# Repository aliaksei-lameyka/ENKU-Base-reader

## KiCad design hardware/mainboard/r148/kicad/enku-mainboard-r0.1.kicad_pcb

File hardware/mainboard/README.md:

# ENKU Base mainboard

Current working PCB **R144 / NO FAB**, branch `engineering/r144-power-margin`. [Project](r144/kicad/enku-mainboard-r0.1.kicad_pro), [review packet](r144/pcbway/), [source/checkpoint](r144/README.md), [current status](../../docs/CURRENT_STATUS.md).

TPS3890 reset + nominal3.220352V PWM supply. Full native/independent local and [server verification](https://github.com/aliaksei-lameyka/ENKU-Base-reader/actions/runs/38693384483) passed. Initial/solder static reserves pass; lifetime/dynamic, FPC/pack/process/firmware and physical tests remain open. See [risks](../../docs/STARTUP_RISKS_R144.md), [FPC](../../docs/FPC_CONNECTOR_REVIEW_R144.md), [pilot FCT](../../docs/FCT_PLAN_R144.md). Physical tests NOT RUN. No case-thickness increase or Base dock/frontlight/Hall/Qi.

`kicad/` is immutable R138. R141/R142/R143 are historical controls. No historical guard/golden was changed. Hardware CERN-OHL-W-2.0, automation MIT.

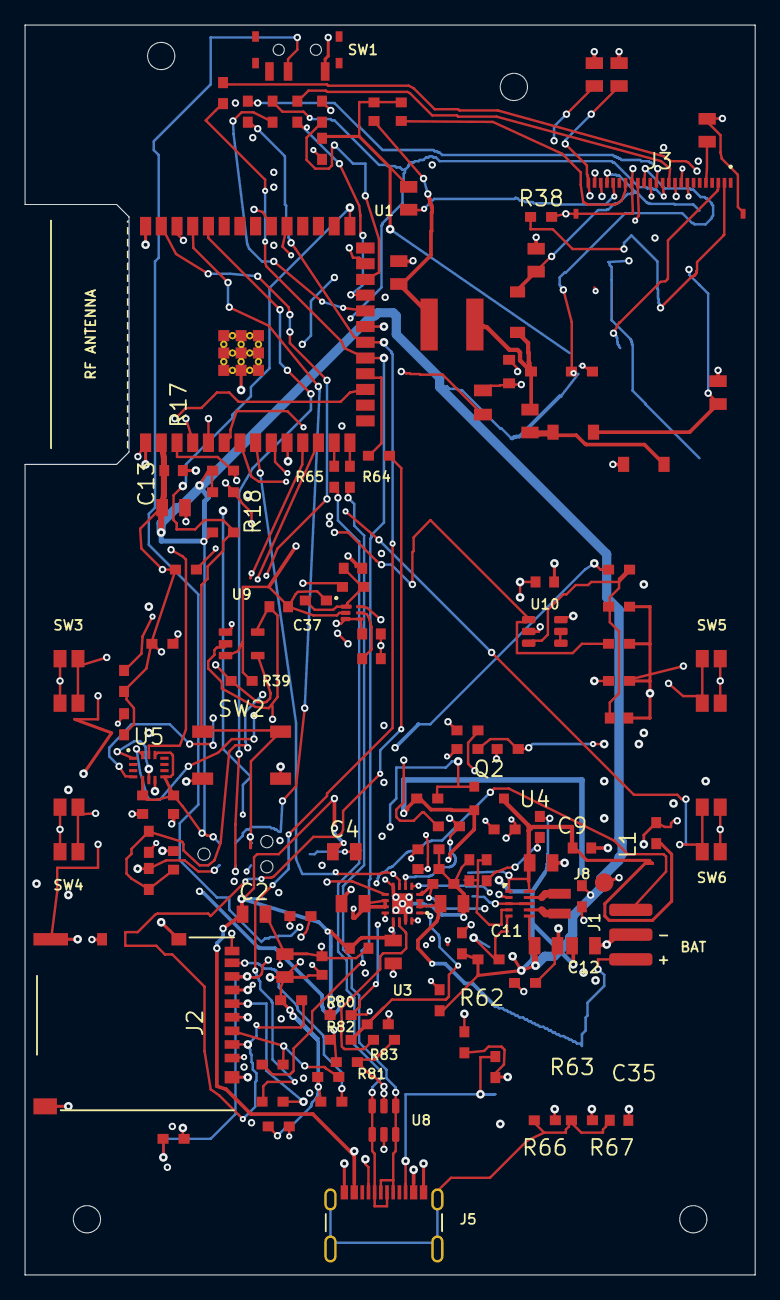
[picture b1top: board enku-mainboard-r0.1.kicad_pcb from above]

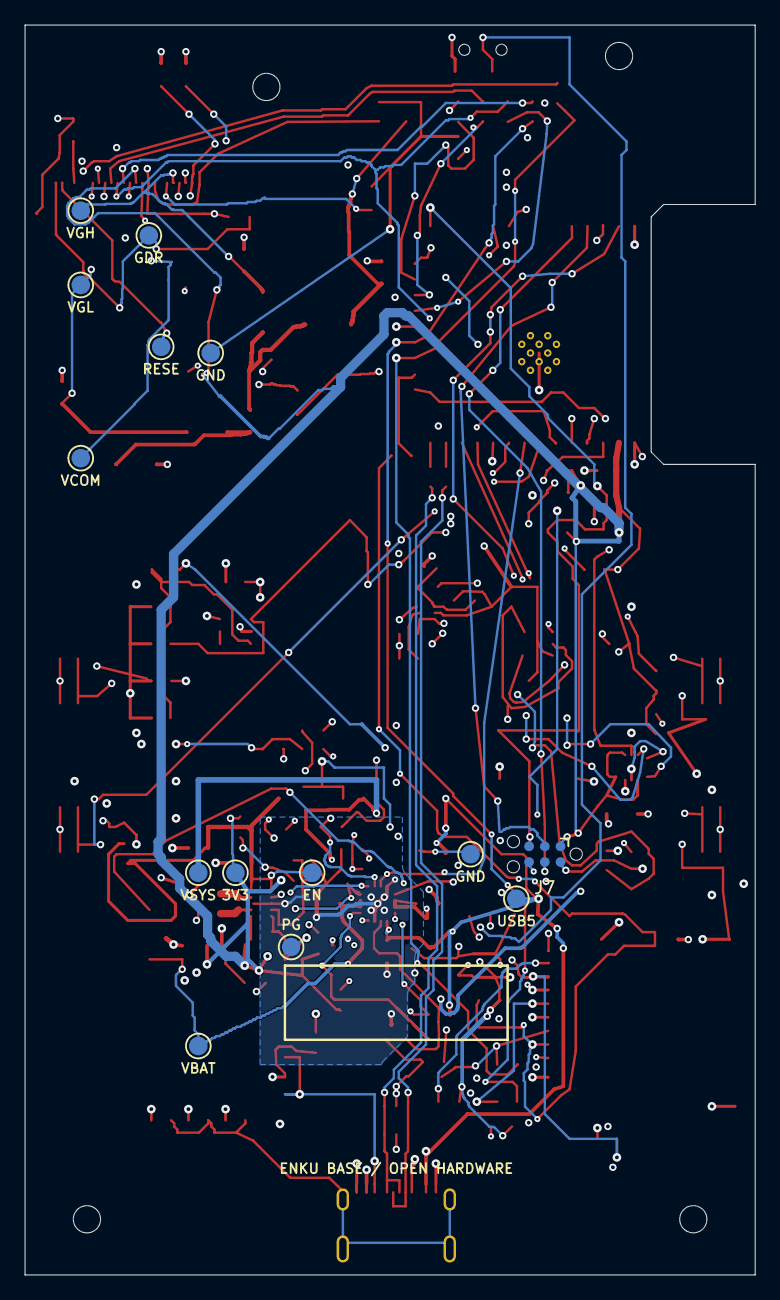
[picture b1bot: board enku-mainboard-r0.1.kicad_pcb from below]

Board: 4 copper layers, 59.0 x 101.0 mm, 141 parts (14 on the bottom side), 84 nets.

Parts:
C2: 1uF 10V; C_CC0805_YAGEO_REFLOW_TRANSFER
C4: 1uF 25V; C_CC0805_YAGEO_REFLOW_TRANSFER
C5, C24, C25, C26, C27, C28, C29, C31: 4.7uF 25V; C_CC0805_YAGEO_REFLOW_TRANSFER
C6: 100nF 25V; C_CC0603_YAGEO_REFLOW_TRANSFER
C7, C8, C9, C11, C12: 22uF 10V; C_CC0805_YAGEO_REFLOW_TRANSFER
C10, C14, C15, C17, C18, C19, C21, C40: 100nF; C_CC0603_YAGEO_REFLOW_TRANSFER
C13, C16: 10uF 10V; C_CC0805_YAGEO_REFLOW_TRANSFER
C22, C23: 1uF 25V; C_CC0603_YAGEO_REFLOW_TRANSFER
C30: 1uF 25V X7R; C_CC0805_YAGEO_REFLOW_TRANSFER
C35: 4.7nF; C_CC0603_YAGEO_REFLOW_TRANSFER
C37, C38: 100nF 10V; C_CC0603_YAGEO_REFLOW_TRANSFER
C39: 1nF C0G 10V; C_CC0603_YAGEO_REFLOW_TRANSFER
C41: 1nF 50V; C_CC0603_YAGEO_REFLOW_TRANSFER
D1, D2, D3: MBR0530T1G; MBR0530T1G_ONSEMI_CASE425H
H1, H2, H3, H4: MOUNT_HOLE_D2_2_BOARD_ONLY
J1: BATTERY_WIRES; BATTERY_WIRE_PADS_2x1x3p5_P2_NO_PASTE
J2: Hirose DM3AT-SF-PEJM5; MICROSD_DM3AT_ENKU
J3: FH34SRJ-24S-0.5SH(50); FH34SRJ-24S-0.5SH
J5: GCT USB4215-03-A; USB4215_03_A_GCT_REVA
J7: Tag-Connect TC2030-IDC-NL; TC2030_NL_CONTACTS_PIN1
J8: External cell NTC / hand solder; NTC_WIRE_TERMINALS_TS_BAR_GND_NO_PASTE
L1: 0.47uH DFE201612E-R47M=P2; Murata_DFE201612E
L2: 47uH TYS5040470M-10; TYS5040_LAIRD_G42_T14_H23
Q1: IRLML6346TRPBF; IRLML6346_INFINEON_MICRO3
Q2: AO3401A; AO3401A_AOS_SOT23
R8: 3.48k 1%; R_RC0603_YAGEO_REFLOW
R9: 2k 1%; R_RC0603_YAGEO_REFLOW
R10, R13, R16, R35, R36, R72: 100k; R_RC0603_YAGEO_REFLOW
R11, R12, R17, R18, R23, R90, R91, R92, R93, R94: 10k; R_RC0603_YAGEO_REFLOW
R14: 27.4k 0.1% 10ppm; R_RT0603_YAGEO_REFLOW
R15: 5.11k 0.1% 10ppm; R_RT0603_YAGEO_REFLOW
R19, R28, R29, R97: 0R; R_RC0603_YAGEO_REFLOW
R20, R21, R22, R64, R65: 0R (22R tune); R_RC0603_YAGEO_REFLOW
R24, R25: 4.7k; R_RC0603_YAGEO_REFLOW
R26: 2M 1%; R_RC0603_YAGEO_REFLOW
R27: 680k 1%; R_RC0603_YAGEO_REFLOW
R30, R31, R32, R33, R34: 22R; R_RC0603_YAGEO_REFLOW
R37: 2.2R 1% 0805; R_CRCW0805_HP_VISHAY_REFLOW
R38: 1M 1%; R_RC0603_YAGEO_REFLOW
R39, R66: 1M; R_RC0603_YAGEO_REFLOW
R40, R82: 100k 1%; R_RC0603_YAGEO_REFLOW
R62, R63: 5.1k 1%; R_RC0603_YAGEO_REFLOW
R67: 0R DNP; R_RC0603_YAGEO_REFLOW_DNP_NO_PASTE
R70: 26.7k 0.1% 25ppm; R_RT0603_YAGEO_REFLOW
R71: 10k 0.1% 25ppm; R_RT0603_YAGEO_REFLOW
R73: 3.3k 1%; R_RC0603_YAGEO_REFLOW
R80: 40.2k 1%; R_RC0603_YAGEO_REFLOW
R81: 33.2k 1%; R_RC0603_YAGEO_REFLOW
R83: 69.8k 1%; R_RC0603_YAGEO_REFLOW
R84, R85: 2.2k 1%; R_RC0603_YAGEO_REFLOW
R86, R87, R88: 1k 1%; R_RC0603_YAGEO_REFLOW
R89: 3.3M 1%; R_RC0603_YAGEO_REFLOW
R95: 16.5k 0.1% 10ppm; R_RT0603_YAGEO_REFLOW
R96: 10k 0.1% 10ppm; R_RT0603_YAGEO_REFLOW
R98: 402R 0.1% 10ppm; R_RT0603_YAGEO_REFLOW
R99: 0R; R_RC0603_YAGEO_REFLOW_DNP_NO_PASTE
SW1: MK-12C03-G015; GSWITCH_MK12C03_G015_DRAWING_REVIEW
SW2: BOOT / RECOVERY; TL3342F160QG_ESWITCH_P010632J
SW3, SW4, SW5, SW6: TL1016AAF160QG; TL1016AAF160QG_ESWITCH_P520001
TP1, TP14: GND; SERVICE_PAD_D1_5_NO_PASTE
TP2: VBUS_USB; SERVICE_PAD_D1_5_NO_PASTE
TP4: VBAT; SERVICE_PAD_D1_5_NO_PASTE
TP5: VSYS; SERVICE_PAD_D1_5_NO_PASTE
TP6: 3V3_SYS; SERVICE_PAD_D1_5_NO_PASTE
TP7: SYS_EN; SERVICE_PAD_D1_5_NO_PASTE
TP8: REG_PG; SERVICE_PAD_D1_5_NO_PASTE
TP9: EPD_GDR; SERVICE_PAD_D1_5_NO_PASTE
TP10: EPD_RESE; SERVICE_PAD_D1_5_NO_PASTE
TP11: EPD_VGH; SERVICE_PAD_D1_5_NO_PASTE
TP12: EPD_VGL; SERVICE_PAD_D1_5_NO_PASTE
TP13: EPD_VCOM; SERVICE_PAD_D1_5_NO_PASTE
U1: ESP32-S3-WROOM-1-N16R8; ESP32_S3_WROOM_1_N16R8_EP_GRID_03_TENT_REQUEST
U3: BQ24072TRGTR; BQ24072T_RGT0016C_TI
U4: TPS63802DLAR; TPS63802_DLA0010A_SPLIT_PASTE
U5: BMI270; BMI270_Bosch_LGA14
U8: USBLC6-2SC6; USBLC6_2SC6_ST_SOT23_6L
U9: TMUX1101DBVR; TMUX1101_TI_DBV0005A
U10: TLV3012BIDBVR; TLV3012B_DBV0006A
U11: TPS389001DSER; TPS3890_TI_DSE0006A_SMD_LEFT

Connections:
3V3_SYS: C11.1, C12.1, C13.1, C14.1, C15.1, C16.1, C17.1, C18.1, C19.1, C38.1, J2.4, J3.15, J7.1, R11.1, R12.1, R16.1, R17.1, R18.1, R23.1, R24.1, R25.1, R28.1, R35.1, R36.1, R39.1, R90.1, R91.1, R92.1, R93.1, R94.1, R95.1, R97.1, R98.1, TP6.1, U1.2, U4.6, U5.5, U5.8, U5.12, U9.4, U10.6, U11.3, U11.4
BAT_ADC: C21.1, R26.2, R27.1, U1.39
BAT_ADC_SW: R26.1, U9.1
BAT_TS: J8.1, R80.2, R81.1, R82.1
BOOT: J7.5, R18.2, SW2.1, U1.27
BTN_L1: SW3.1, SW3.2, U1.4
BTN_L2: SW4.1, SW4.2, U1.5
BTN_R1: SW5.1, SW5.2, U1.6
BTN_R2: SW6.1, SW6.2, U1.7
CHG_CE_CMD: R88.1, U1.31
CHG_CE_N: R10.1, R88.2, U3.4
CHG_EN1: R84.1, R86.2, U3.6
CHG_EN1_CMD: R86.1, U1.9
CHG_EN2: R85.1, R87.2, U3.5
CHG_EN2_CMD: R87.1, U1.38
CHG_ILIM_VSET: R8.1, U3.12
CHG_ISET: R9.1, U3.16
CHG_STAT1: R11.2, U1.8, U3.7
CHG_STAT2: R12.2, U3.9
CHG_TMR: R83.1, U3.14
CHG_TS: R82.2, R89.1, U3.1
EPD_BS1: J3.8, R29.1
EPD_BUSY: J3.9, U1.25
EPD_CP_NEG: C25.2, D2.2, D3.1
EPD_CS: R32.1, U1.22
EPD_CS_PANEL: J3.12, R32.2, R35.2
EPD_DC: R31.1, U1.23
EPD_DC_PANEL: J3.11, R31.2
EPD_GDR: J3.2, Q1.1, R38.1, TP9.1
EPD_MOSI_PANEL: J3.14, R34.2
EPD_RESE: J3.3, Q1.2, R37.1, TP10.1
EPD_RST: R30.1, U1.24
EPD_RST_PANEL: J3.10, R30.2, R36.2
EPD_SCLK_PANEL: J3.13, R33.2
EPD_SW: C25.1, D1.2, L2.2, Q1.3
EPD_VCI: C22.1, C31.1, J3.16, L2.1, R28.2
EPD_VCOM: C30.1, J3.24, TP13.1
EPD_VDD: C23.1, J3.18
EPD_VGH: C24.1, D1.1, J3.21, TP11.1
EPD_VGL: C26.1, D3.2, J3.23, TP12.1
EPD_VSH1: C27.1, J3.20
EPD_VSH2: C28.1, J3.5
EPD_VSL: C29.1, J3.22
ESP_EN: J7.6, R17.2, U1.3, U11.6
GND: C2.2, C4.2, C5.2, C6.2, C7.2, C8.2, C9.2, C10.2, C11.2, C12.2, C13.2, C14.2, C15.2, C16.2, C17.2, C18.2, C19.2, C21.2, C22.2, C23.2, C24.2, C26.2, C27.2, C28.2, C29.2, C30.2, C31.2, C35.2, C37.2, C38.2, C39.2, C40.2, C41.2, D2.1, J1.2, J2.6, J2.10 (CD_B), J3.17, J3.S1, J3.S2, J5.A1, J5.A12, J5.B1, J5.B12, J7.2, J8.2, R8.2, R9.2, R10.2, R13.2, R15.2, R27.2, R29.2, R37.2, R38.2, R39.2, R62.2, R63.2, R66.2, R67.2, R71.2, R72.2, R73.2, R81.2, R83.2, R84.2, R85.2, R89.2, R96.2, R99.2, SW1.1, SW2.2, SW3.3, SW3.4, SW4.3, SW4.4, SW5.3, SW5.4, SW6.3, SW6.4, TP1.1, TP14.1, U1.1, U1.40, U1.41, U3.8, U3.15, U3.17, U4.3, U4.8, U5.1, U5.6, U5.7, U8.2, U9.3, U10.2, U11.2
I2C_SCL: R25.2, U1.17, U5.13
I2C_SDA: R24.2, U1.12, U5.14
IMU_INT1: U1.11, U5.4
PWR_GATE: Q2.1, R40.2, SW1.2
REG_FB: R14.2, R15.1, U4.4
REG_FB_TOP: R14.1, R98.2
REG_L1: L1.1, U4.9
REG_L2: L1.2, U4.7
REG_MODE: R97.2, R99.1, U4.2
REG_PG: R16.2, TP8.1, U4.5
RESET_CT: C40.1, U11.5
RESET_SENSE: C41.1, R95.2, R96.1, U11.1
SD_CD: J2.9 (CD_A), R90.2, U1.32
SD_CS: R19.1, U1.18
SD_CS_CARD: J2.2, R19.2, R23.2
SD_DAT1_BIAS: J2.8, R93.2
SD_DAT2_BIAS: J2.1, R94.2
SD_MISO_CARD: J2.7, R22.1, R92.2
SD_MOSI_CARD: J2.3, R20.2, R91.2
SD_SCLK_CARD: J2.5, R21.2
SPI_MISO: R22.2, U1.21
SPI_MOSI: R20.1, R34.1, U1.19
SPI_SCLK: R21.1, R33.1, U1.20
SYS_EN: C9.1, C10.1, Q2.3, R13.1, TP7.1, U4.1, U4.10
UART_RX: J7.4, U1.36
UART_TX: J7.3, U1.37
USB_CC1: J5.A5, R62.1
USB_CC2: J5.B5, R63.1
USB_DM: R65.2, U1.13
USB_DM_CONN: J5.A7, J5.B7, R65.1, U8.3, U8.4
USB_DP: R64.2, U1.14
USB_DP_CONN: J5.A6, J5.B6, R64.1, U8.1, U8.6
USB_SHIELD: C35.1, J5.S, R66.1, R67.1
USB_VBUS_DIV: C39.1, R70.2, R71.1, U10.3
USB_VBUS_REF: U10.4, U10.5
USB_VBUS_VALID: R72.1, U1.10, U10.1
VBAT: C8.1, C37.1, J1.1, TP4.1, U3.2, U3.3, U9.2, U9.5
VBUS_USB: C2.1, C4.1, C5.1, C6.1, J5.A4, J5.A9, J5.B4, J5.B9, R70.1, R73.1, R80.1, TP2.1, U3.13, U8.5
VSYS: C7.1, Q2.2, R40.1, TP5.1, U3.10, U3.11

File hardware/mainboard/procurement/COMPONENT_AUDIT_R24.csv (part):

"ref","value","footprint","side","x_mm","y_mm","rotation_deg","manufacturer","mpn_candidate","preferred_source","manufacturer_drawing","status","footprint_checked","pinout_checked","orientation_checked","cad_checked","pcbway_sourcing_confirmed","review_note"
"C1","100nF","Capacitor_SMD:C_0603_1608Metric","F","64","79","0","","","","","UNSELECTED","NO","NO","NO","NO","NO","Exact orderable passive MPN/voltage/tolerance not selected"
"C2","10uF 10V","Capacitor_SMD:C_0805_2012Metric","F","36.5","92.5","0","","","","","UNSELECTED","NO","NO","NO","NO","NO","Exact orderable passive MPN/voltage/tolerance not selected"
"C3","10uF 10V","Capacitor_SMD:C_0805_2012Metric","F","40","93","0","","","","","UNSELECTED","NO","NO","NO","NO","NO","Exact orderable passive MPN/voltage/tolerance not selected"
"C4","10uF 10V","Capacitor_SMD:C_0805_2012Metric","F","43.8","86.8","0","","","","","UNSELECTED","NO","NO","NO","NO","NO","Exact orderable passive MPN/voltage/tolerance not selected"
"C5","4.7uF 25V","Capacitor_SMD:C_0805_2012Metric","F","45.5","88.5","0","","","","","UNSELECTED","NO","NO","NO","NO","NO","Exact orderable passive MPN/voltage/tolerance not selected"
"C6","100nF 25V","Capacitor_SMD:C_0603_1608Metric","F","47.35","87.75","270","","","","","UNSELECTED","NO","NO","NO","NO","NO","Exact orderable passive MPN/voltage/tolerance not selected"
"C7","10uF 25V","Capacitor_SMD:C_0805_2012Metric","F","51.0","93.5","90","","","","","UNSELECTED","NO","NO","NO","NO","NO","Exact orderable passive MPN/voltage/tolerance not selected"
"C8","4.7uF 10V","Capacitor_SMD:C_0805_2012Metric","F","48.5","93.6","180","","","","","UNSELECTED","NO","NO","NO","NO","NO","Exact orderable passive MPN/voltage/tolerance not selected"
"C9","10uF 10V","Capacitor_SMD:C_0805_2012Metric","F","59.7","87.7","0","","","","","UNSELECTED","NO","NO","NO","NO","NO","Exact orderable passive MPN/voltage/tolerance not selected"
"C10","100nF","Capacitor_SMD:C_0603_1608Metric","F","63","86.5","0","","","","","UNSELECTED","NO","NO","NO","NO","NO","Exact orderable passive MPN/voltage/tolerance not selected"
"C11","22uF 10V","Capacitor_SMD:C_0805_2012Metric","F","60.1","94.4","0","","","","","UNSELECTED","NO","NO","NO","NO","NO","Exact orderable passive MPN/voltage/tolerance not selected"
"C12","22uF 10V","Capacitor_SMD:C_0805_2012Metric","F","63.3","94.4","0","","","","","UNSELECTED","NO","NO","NO","NO","NO","Exact orderable passive MPN/voltage/tolerance not selected"
"C13","10uF 10V","Capacitor_SMD:C_0805_2012Metric","F","23.8","56.2","0","","","","","UNSELECTED","NO","NO","NO","NO","NO","Exact orderable passive MPN/voltage/tolerance not selected"
"C14","100nF","Capacitor_SMD:C_0603_1608Metric","F","27","56.2","0","","","","","UNSELECTED","NO","NO","NO","NO","NO","Exact orderable passive MPN/voltage/tolerance not selected"
"C15","1uF","Capacitor_SMD:C_0603_1608Metric","F","26.5","58.5","0","","","","","UNSELECTED","NO","NO","NO","NO","NO","Exact orderable passive MPN/voltage/tolerance not selected"
"C16","10uF 10V","Capacitor_SMD:C_0805_2012Metric","F","39","96","90","","","","","UNSELECTED","NO","NO","NO","NO","NO","Exact orderable passive MPN/voltage/tolerance not selected"
"C17","100nF","Capacitor_SMD:C_0603_1608Metric","F","42","96","90","","","","","UNSELECTED","NO","NO","NO","NO","NO","Exact orderable passive MPN/voltage/tolerance not selected"
"C18","100nF","Capacitor_SMD:C_0603_1608Metric","F","22","77","90","","","","","UNSELECTED","NO","NO","NO","NO","NO","Exact orderable passive MPN/voltage/tolerance not selected"
"C19","100nF","Capacitor_SMD:C_0603_1608Metric","F","24","80","90","","","","","UNSELECTED","NO","NO","NO","NO","NO","Exact orderable passive MPN/voltage/tolerance not selected"
"C20","100nF","Capacitor_SMD:C_0603_1608Metric","F","72","52","90","","","","","UNSELECTED","NO","NO","NO","NO","NO","Exact orderable passive MPN/voltage/tolerance not selected"
"C21","100nF","Capacitor_SMD:C_0603_1608Metric","F","30","87.5","90","","","","","UNSELECTED","NO","NO","NO","NO","NO","Exact orderable passive MPN/voltage/tolerance not selected"
"C22","1uF 25V","Capacitor_SMD:C_0603_1608Metric","F","46.2","27","90","","","","","UNSELECTED","NO","NO","NO","NO","NO","Exact orderable passive MPN/voltage/tolerance not selected"
"C23","1uF 25V","Capacitor_SMD:C_0603_1608Metric","F","48.4","27","90","","","","","UNSELECTED","NO","NO","NO","NO","NO","Exact orderable passive MPN/voltage/tolerance not selected"
"C24","4.7uF 25V","Capacitor_SMD:C_0805_2012Metric","F","48.0","42.0","90","","","","","UNSELECTED","NO","NO","NO","NO","NO","Exact orderable passive MPN/voltage/tolerance not selected"
"C25","4.7uF 25V","Capacitor_SMD:C_0805_2012Metric","F","58","52","0","","","","","UNSELECTED","NO","NO","NO","NO","NO","Exact orderable passive MPN/voltage/tolerance not selected"
"C26","4.7uF 25V","Capacitor_SMD:C_0805_2012Metric","F","24.0","64.0","0","","","","","UNSELECTED","NO","NO","NO","NO","NO","Exact orderable passive MPN/voltage/tolerance not selected"
"C27","4.7uF 25V","Capacitor_SMD:C_0805_2012Metric","F","49","34","90","","","","","UNSELECTED","NO","NO","NO","NO","NO","Exact orderable passive MPN/voltage/tolerance not selected"
"C28","4.7uF 25V","Capacitor_SMD:C_0805_2012Metric","F","61","34","90","","","","","UNSELECTED","NO","NO","NO","NO","NO","Exact orderable passive MPN/voltage/tolerance not selected"
"C29","4.7uF 25V","Capacitor_SMD:C_0805_2012Metric","F","64","39","90","","","","","UNSELECTED","NO","NO","NO","NO","NO","Exact orderable passive MPN/voltage/tolerance not selected"
"C30","1uF 25V X7R","Capacitor_SMD:C_0805_2012Metric","F","66","39","90","","","","","UNSELECTED","NO","NO","NO","NO","NO","Exact orderable passive MPN/voltage/tolerance not selected"
"C31","4.7uF 25V","Capacitor_SMD:C_0805_2012Metric","F","28.0","64.0","90","","","","","UNSELECTED","NO","NO","NO","NO","NO","Exact orderable passive MPN/voltage/tolerance not selected"
"C35","4.7nF","Capacitor_SMD:C_0603_1608Metric","F","66","108.5","0","","","","","UNSELECTED","NO","NO","NO","NO","NO","Exact orderable passive MPN/voltage/tolerance not selected"
"C36","10nF","Capacitor_SMD:C_0603_1608Metric","B","65.0","98.0","90","","","","","UNSELECTED","NO","NO","NO","NO","NO","Exact orderable passive MPN/voltage/tolerance not selected"
"D1","MBR0530","Diode_SMD:D_SOD-123","F","49","44","90","","","","","UNSELECTED","NO","NO","NO","NO","NO","Exact orderable passive MPN/voltage/tolerance not selected"
"D2","MBR0530","Diode_SMD:D_SOD-123","F","56","49","0","","","","","UNSELECTED","NO","NO","NO","NO","NO","Exact orderable passive MPN/voltage/tolerance not selected"
"D3","MBR0530","Diode_SMD:D_SOD-123","F","52","48","0","","","","","UNSELECTED","NO","NO","NO","NO","NO","Exact orderable passive MPN/voltage/tolerance not selected"
"H1","","MountingHole:MountingHole_2.2mm_M2","F","30","23","0","","","","","PCB_FEATURE","NO","NO","NO","NO","NO","Requires vendor dimensional, pin, orientation, 3D, PCBWay sourcing review"
"H2","","MountingHole:MountingHole_2.2mm_M2","F","71","23","0","","","","","PCB_FEATURE","NO","NO","NO","NO","NO","Requires vendor dimensional, pin, orientation, 3D, PCBWay sourcing review"
"H3","","MountingHole:MountingHole_2.2mm_M2","F","23","111","0","","","","","PCB_FEATURE","NO","NO","NO","NO","NO","Requires vendor dimensional, pin, orientation, 3D, PCBWay sourcing review"
"H4","","MountingHole:MountingHole_2.2mm_M2","F","71","111","0","","","","","PCB_FEATURE","NO","NO","NO","NO","NO","Requires vendor dimensional, pin, orientation, 3D, PCBWay sourcing review"
"J1","1S LiPo + NTC","Connector_Generic:JST_PH_3_PLACEMENT","F","66","93.5","90","JST candidate","S3B-PH-SM4-TB","","","PLACEHOLDER","NO","NO","NO","NO","NO","Supplier real footprint/pinout missing"
"J2","Hirose DM3AT-SF-PEJM5","ENKU:MICROSD_DM3AT_ENKU","F","28.9","100.7","90","Hirose","DM3AT-SF-PEJM5","","https://www.hirose.com/en/product/p/CL0609-0031-0-00","IDENTIFIED","NO","NO","NO","NO","NO","Known board access / edge orientation blocker"
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
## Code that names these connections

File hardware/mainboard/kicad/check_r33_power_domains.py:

#!/usr/bin/env python3
"""R33 source-level switched VIN + Good Display 24-pin hard release block."""
import argparse
import re
from pathlib import Path
HERE=Path(__file__).parent
PCB=(HERE/"enku-mainboard-r1.0-base-switched-vin.kicad_pcb").read_text()
SCH=(HERE/"power.kicad_sch").read_text()
EPD=(HERE/"epd_hv.kicad_sch").read_text()
def balanced(src,start):
    depth=0; quoted=False; escaped=False
    for i in range(start,len(src)):
        c=src[i]
        if quoted:
            if escaped: escaped=False
            elif c=="\\": escaped=True
            elif c=='"': quoted=False
        elif c=='"': quoted=True
        elif c=='(': depth+=1
        elif c==')':
            depth-=1
            if depth==0:return src[start:i+1]
    raise ValueError("Unbalanced footprint")
def fp(ref):
    p=PCB.index('(property "Reference" "'+ref+'"')
    return balanced(PCB,PCB.rfind("(footprint ",0,p))
def pad(ref,num):
    lines=[l for l in fp(ref).splitlines() if '(pad "'+str(num)+'" ' in l]
    assert len(lines)==1,(ref,num,len(lines))
    m=re.search(r'\(net \d+ "([^"]+)"\)',lines[0])
    return m[1] if m else "NC"
def main():
    cli=argparse.ArgumentParser()
    cli.add_argument("--release",action="store_true")
    args=cli.parse_args()
    assert PCB.count('(footprint "')==120
    assert not re.search(r'(?m)^  \((segment|via|zone)\b',PCB)
    nets={("SW1","1"):"VSYS",("SW1","2"):"SYS_EN",
          ("U4","1"):"SYS_EN",("U4","10"):"SYS_EN",
          ("C9","1"):"SYS_EN",("C9","2"):"GND",
          ("C10","1"):"SYS_EN",("C10","2"):"GND",
          ("R13","1"):"SYS_EN",("R13","2"):"GND",
          ("U3","1"):"VSYS",("TP5","1"):"VSYS",("TP7","1"):"SYS_EN",
          ("R26","1"):"VBAT",("R26","2"):"BAT_ADC",
          ("R27","1"):"BAT_ADC",("R27","2"):"GND"}
    for (ref,num),expected in nets.items():
        assert pad(ref,num)==expected,(ref,num,pad(ref,num),expected)
    for coord in ("187.96 57.15","243.84 62.23","243.84 85.09"):
        assert f'(global_label "SYS_EN" (shape input) (at {coord} 0)' in SCH,coord
    pins={1:"NC",2:"EPD_GDR",3:"EPD_RESE",4:"NC",5:"EPD_VSH2",
          6:"NC",7:"NC",8:"EPD_BS1",9:"EPD_BUSY",10:"EPD_RST_PANEL",
          11:"EPD_DC_PANEL",12:"EPD_CS_PANEL",13:"EPD_SCLK_PANEL",
          14:"EPD_MOSI_PANEL",15:"3V3_SYS",16:"EPD_VCI",17:"GND",
          18:"EPD_VDD",19:"NC",20:"EPD_VSH1",21:"EPD_VGH",
          22:"EPD_VSL",23:"EPD_VGL",24:"EPD_VCOM"}
    for num,expected in pins.items():
        assert pad("J3",str(num))==expected,(num,pad("J3",str(num)),expected)
    assert pad("R28","1")=="3V3_SYS" and pad("R28","2")=="EPD_VCI"
    assert '(property "Value" "0R"' in fp("R28")
    r28=balanced(EPD,EPD.index('(symbol (lib_id "ENKU:R") (at 190.5 44.45'))
    assert '(dnp no)' in r28
    print("R33 POWER+EPD SOURCE PASS: 120 parts; BQ25185 VSYS switched through SW1 to U4 VIN+EN+Cin; 24-pin J3 and R28 0R checked.")
    print("RELEASE BLOCKED: VBAT/ADC unpowered-MCU backfeed, switch MPN/contact rating, EPD pin5 VDHR/VSH2 vendor contradiction and real FPC fold, off-state bench.")
    if args.release:raise SystemExit("FAB BLOCKED: physical electrical signoff required")
if __name__=="__main__":main()
